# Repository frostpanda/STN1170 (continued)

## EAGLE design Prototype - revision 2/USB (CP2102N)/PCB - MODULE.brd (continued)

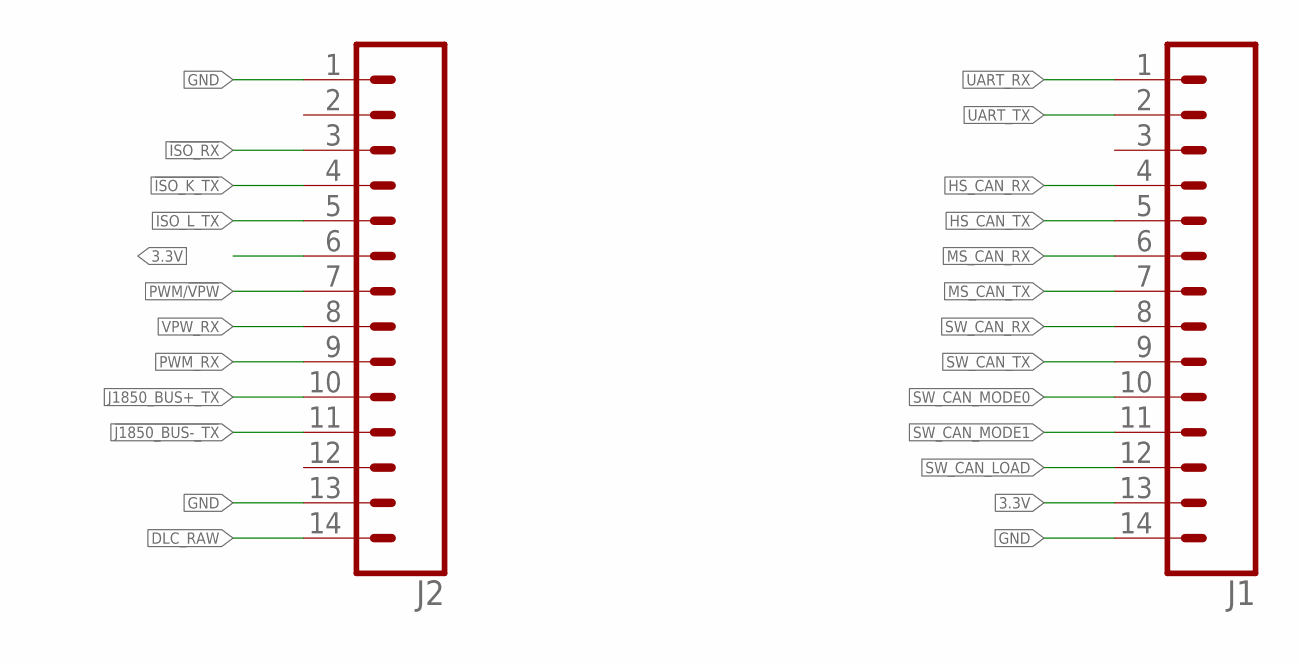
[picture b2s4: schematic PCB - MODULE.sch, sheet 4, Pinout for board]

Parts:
J1, J2: CONN_14; 1X14

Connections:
3.3V: J1.13, J2.6; also elsewhere on the board
!ISO_K_TX: J2.4; also elsewhere on the board
!ISO_L_TX: J2.5; also elsewhere on the board
!ISO_RX: J2.3; also elsewhere on the board
!J1850_BUS-_TX: J2.11; also elsewhere on the board
DLC_RAW: J2.14; also elsewhere on the board
GND: J1.14, J2.1, J2.13; also elsewhere on the board
HS_CAN_RX: J1.4; also elsewhere on the board
HS_CAN_TX: J1.5; also elsewhere on the board
J1850_BUS+_TX: J2.10; also elsewhere on the board
MS_CAN_RX: J1.6; also elsewhere on the board
MS_CAN_TX: J1.7; also elsewhere on the board
PWM/!VPW: J2.7; also elsewhere on the board
PWM_RX: J2.9; also elsewhere on the board
SW_CAN_LOAD: J1.12; also elsewhere on the board
SW_CAN_MODE0: J1.10; also elsewhere on the board
SW_CAN_MODE1: J1.11; also elsewhere on the board
SW_CAN_RX: J1.8; also elsewhere on the board
SW_CAN_TX: J1.9; also elsewhere on the board
UART_RX: J1.1; also elsewhere on the board
UART_TX: J1.2; also elsewhere on the board
VPW_RX: J2.8; also elsewhere on the board

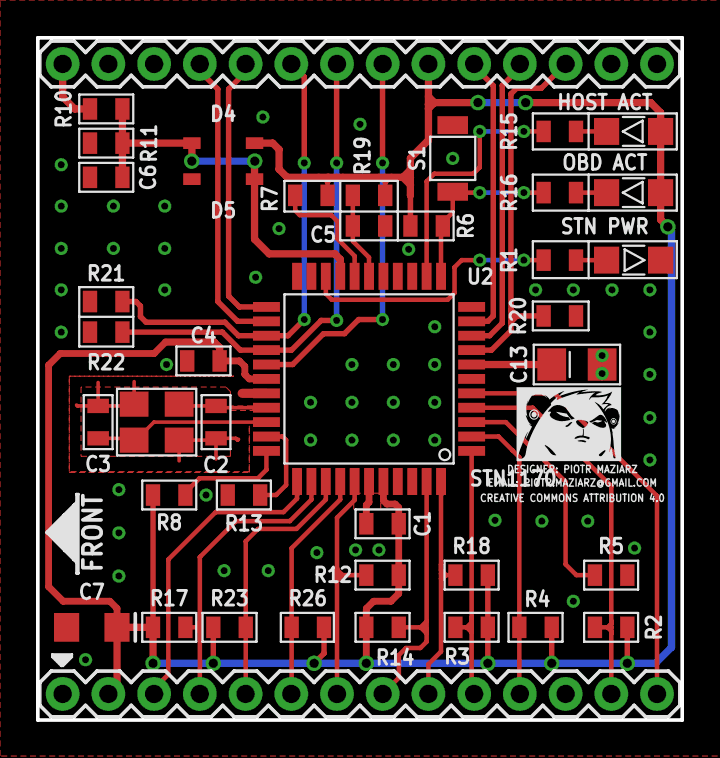
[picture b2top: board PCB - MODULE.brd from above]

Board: 2 copper layers, 35.8 x 37.9 mm, 43 parts (1 on the bottom side), 37 nets.

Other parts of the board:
U$1, U$2: LOGO2

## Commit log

2017-06-21 Release STN1170 daughter board
    Initial release of daughter board
2017-06-21 Release STN1170 module board
    Initial release of module board
2017-06-21 STN1170 prototype (#1)
    STN1170 prototype
2017-06-23 Improvements in PCB layout
    1. Changed old TSX-3225 to version with bigger pads (now soldering should be easier, especially using soldering iron).
    2. Changed layout of a guard ring and crystal with capacitors to match new TSX-3225 pads. Capacitors C2 and C3 now are placed wider than before. This will help with soldering, without worry about STN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
    3. Changed position of R8 and R13 resistors and traces for them. This modification remov
2017-06-23 Fix regulators name
    - Changed LDO names to the original value of the element. Choosed LDO has different pinout, compared to 7805 and LM317 LDO.
    - Future commts will bring back NCP1117 LDO for 5V power line and ZLODO1117-3.3 for 3.3V power line
2017-06-24 Fixes/improvements/replace
    CP2102N:
    -SCHEMATIC:
    1. Changed connection to GND, instead of GND_CP. This will be explained in BOARD section.
    2. Rearranged status LED's and resistor for them and now they are powered by CP2102N integrated LDO instead of 3.3V power line.
    3. Minor improvements in CP2102N sheet schematic readability.
    BOARD:
2017-06-25 3.3V regulator/optimize filter section/others
    Schematic:
    1. Changed MCP1703 LDO regulator to ZLDO1117 regulator.
    2. Changed value of C18 and C19 to 4.7uF.
    Board:
    1. Rearranged regulator position, due to a different pinout.
    2. Changed traces route for DLC going into ZLDO1117 input and output due to different pinout and elements placement.
2017-06-27 Changes/updates
    Schematic:
    1. Changed connection between the CP2102N LED's and IC.
    2. Another minor improvements in CP2102N sheet schematic readability.
    Board:
    1. Relocated CP2102N chip inside the board.
    2. Rearranged C1, C2, C3, C4, D2, J3, R3 components because of new position of the CP2102N.
2017-06-27 Hotfix/changes/optimization
    1. Updated NCP1117 device in schematic and board files. Now it is 100% correct (LOL).
    2. Reroute traces because of fixed pinout of the NCP1117 (LOL).
    3. Some minor improvements in component placement, near LM339 comparator for easier soldering (R25, R26, R39, R41, vias). Easier
    4. Added to connector J6 3.3V power line on pin 6 for R27, R28, and R32 resistors. This allowed to reduce traces on the bottom side of the board.
    5. Changed trace route of K-LINE signal, from T7 to R47 element (matter of esthetics).
    6. Removed bridge from the bottom side of the board, connecting DLC_RAW2 between F5, D32 and D30. The trace was moved to the top layer.
2017-06-27 Add
    Added to the J2 connector on pin 6 3.3V output for resistors, which can be found on daughter board.
2017-06-27 Added .gitignore file
2017-06-28 Improvements
    1. Rearranged position of R7, R23, R29, D7, D22, D24 and D25 for easier soldering.
    2. Reroute signal traces (COMPARATOR+, J1850_BUS-, J1850_BUS+) because of new placement of elements, which was moved. Now this look a little cleaner than before.
    3. K-LLINE signal trace was moved by few millimeters from !ISO_L_TX.
    4. Minor improvements in component placement, near LM339 comparator for easier soldering (R39, R41, vias).
    TO DO:
    1. Because of difficulties to get TJA1048 in my country and NXP do not have this IC in sample program anymore, this part will be changed to 2 independent CAN transceivers in near future.
2017-06-29 K-Line and L-Line optimization/improvements/changes
    1. Changed placement of the R33 and R34 resistors for K-LINE and L-LINE signal traces for future changes in J2 connector.
    2. T7 and T8 are now more separated than before.
    3. Because of above changes was needed to reroute signal traces for K-LINE and L-LINE signal traces.
    4. Changed width of the K-LINE signal trace going from T7 to R42 from 16mils to 12mils.
    5. Changed route for DLC power trace for SW-CAN transceiver.
    6. Added power plane for 3.3V on the top side of the board.
2017-07-08 BM71
    Reimplemented BM71 module.
    Module worked on 1st revision prototype board, but somehow it lost his MAC address after some configuration. This is known issue about this module and it will be changed in future.
    RN4871-V has the same pinout as BM71 and same recommended design, so it can be replaced without any problems.
    In future, board with USB and BT will be separate. For now,to lower the cost of prototype, such arrangement will stay for now.
    TO DO:
    1. Because of difficulties to get TJA1048 in my country and NXP do not have this IC in sample program anymore, this part will be changed to 2 independent CAN transceivers in near future.
2017-07-09 Optimization/fixes
    Schematic:
    1, Fixed D2 and D3 LED's polarization.
    Board:
    1. Elements near U2 IC pushed away to allow easier soldering.
    2. Added S1 switch instead of jumper for NVM reset.
    2. Added cut out for USB connector from daughter board.
2017-07-24 Minor things/Tweaks
    Main board:
    1. Deleted one front name on the top layer of the board.
    2. Added marking for 1st pin on the top of the board to easier recognize, where is front of the PCB.
    Daughter board:
    1. Adder missing 2 vias under 5V LDO. I deleted these two by mistake.
    2. Change position of the power status LED's
2017-07-24 CleanUp
    1. Moved files to the separate folder.
2017-07-24 Set theme jekyll-theme-cayman
2018-08-04 Update README.md
    Updated information about project
2019-01-10 Create licence file
2019-01-10 Create licence file (#4)
2019-01-10 Rename LICENSE to LICENSE.md
2019-01-10 Revision 2 - USB
    First commit for revision 2 prototype, with USB communication. layout.
    Changes:
    1. TJA1048 changed for MCP2562 or TJ1051 (version with Vio pin)
    2. 3.3V LDO is now powered from 5V power source, instead of pure +12V
    3. Routing optimalization
    And others stuff
